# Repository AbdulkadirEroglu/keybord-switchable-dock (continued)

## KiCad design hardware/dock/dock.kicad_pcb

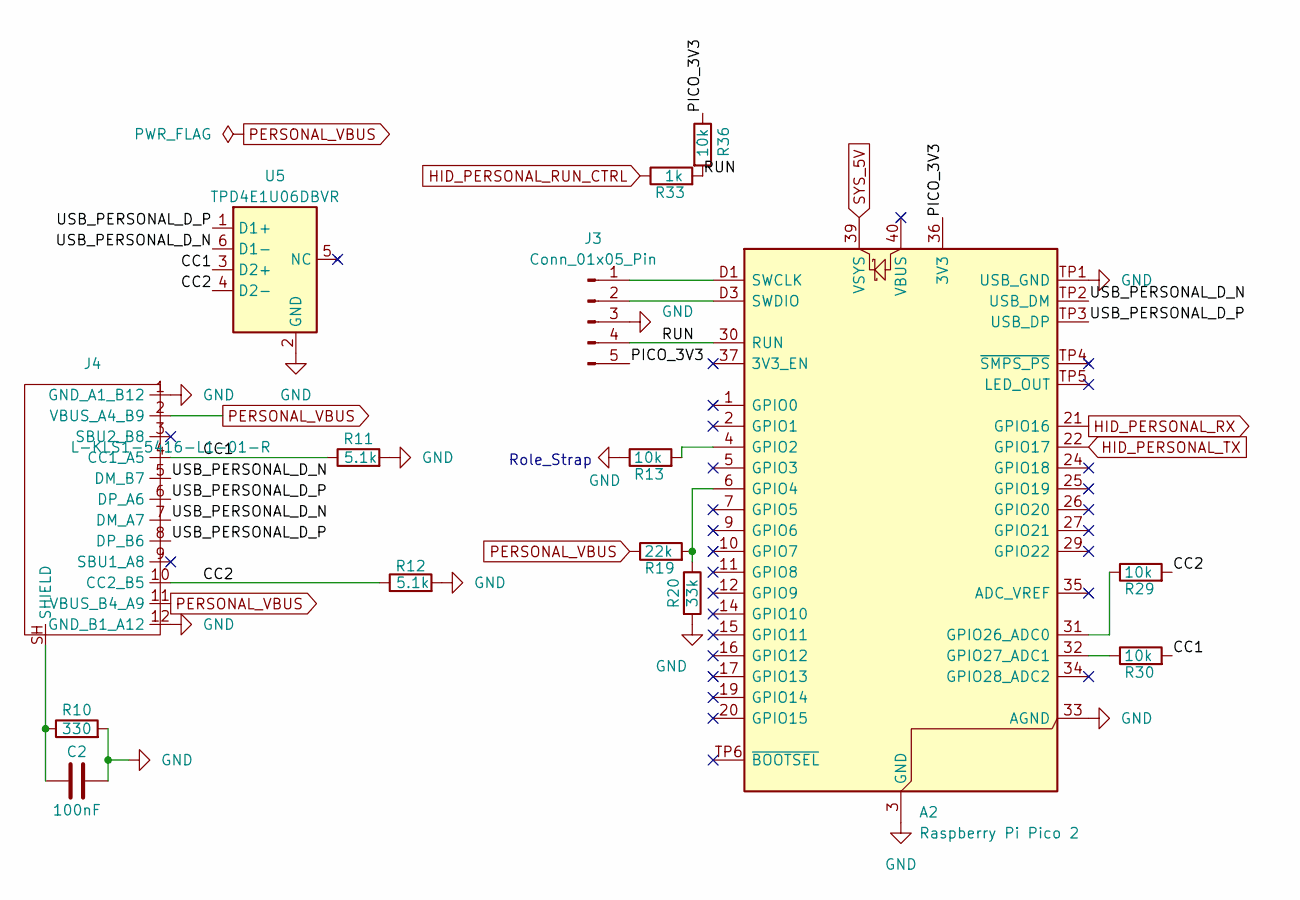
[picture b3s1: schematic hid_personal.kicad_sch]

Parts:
A2: Raspberry Pi Pico 2; RaspberryPi_Pico2_Socket_Pogo
C2: 100nF; C_0805_2012Metric_Pad1.18x1.45mm_HandSolder
J3: Conn_01x05_Pin; PinHeader_1x05_P2.54mm_Vertical
J4: L-KLS1-5416-L1-01-R; KLS L-KLS1-5416-L1-01-R
R10: 330; R_0805_2012Metric_Pad1.20x1.40mm_HandSolder
R11, R12: 5.1k; R_0805_2012Metric_Pad1.20x1.40mm_HandSolder
R13, R29, R30, R36: 10k; R_0805_2012Metric_Pad1.20x1.40mm_HandSolder
R19: 22k; R_0805_2012Metric_Pad1.20x1.40mm_HandSolder
R20: 33k; R_0805_2012Metric_Pad1.20x1.40mm_HandSolder
R33: 1k; R_0805_2012Metric_Pad1.20x1.40mm_HandSolder
U5: TPD4E1U06DBVR; SOT-23-6

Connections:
/HID_PERSONAL/CC1: J4.4 (CC1_A5), R11.1, R30.2, U5.3 (D2+)
/HID_PERSONAL/CC2: J4.10 (CC2_B5), R12.1, R29.2, U5.4 (D2-)
/HID_PERSONAL/PICO_3V3: A2.36 (3V3), J3.5, R36.1
/HID_PERSONAL/RUN: A2.30 (RUN), J3.4, R33.2, R36.2
/HID_PERSONAL/USB_PERSONAL_D_N: A2.TP2 (USB_DM), J4.5 (DM_B7), J4.7 (DM_A7), U5.6 (D1-)
/HID_PERSONAL/USB_PERSONAL_D_P: A2.TP3 (USB_DP), J4.6 (DP_A6), J4.8 (DP_B6), U5.1 (D1+)
GND: A2.3 (GND), A2.8 (GND), A2.13 (GND), A2.18 (GND), A2.23 (GND), A2.28 (GND), A2.33 (AGND), A2.38 (GND), A2.D2 (GND), A2.TP1 (USB_GND), C2.1, J3.3, J4.1 (GND_A1_B12), J4.12 (GND_B1_A12), R10.2, R11.2, R12.2, R13.1, R20.2, U5.2 (GND); also elsewhere on the board
HID_PERSONAL_RUN_CTRL: R33.1; also elsewhere on the board
HID_PERSONAL_RX: A2.21 (GPIO16); also elsewhere on the board
HID_PERSONAL_TX: A2.22 (GPIO17); also elsewhere on the board
unnamed: A2.4 (GPIO2), R13.2
unnamed: A2.6 (GPIO4), R19.2, R20.1
unnamed: A2.31 (GPIO26_ADC0), R29.1
unnamed: A2.32 (GPIO27_ADC1), R30.1
unnamed: A2.D1 (SWCLK), J3.1
unnamed: A2.D3 (SWDIO), J3.2
unnamed: C2.2, J4.SH (SHIELD), R10.1
PERSONAL_VBUS: J4.2 (VBUS_A4_B9), J4.11 (VBUS_B4_A9), R19.1; also elsewhere on the board
SYS_5V: A2.39 (VSYS); also elsewhere on the board

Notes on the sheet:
Role_Strap

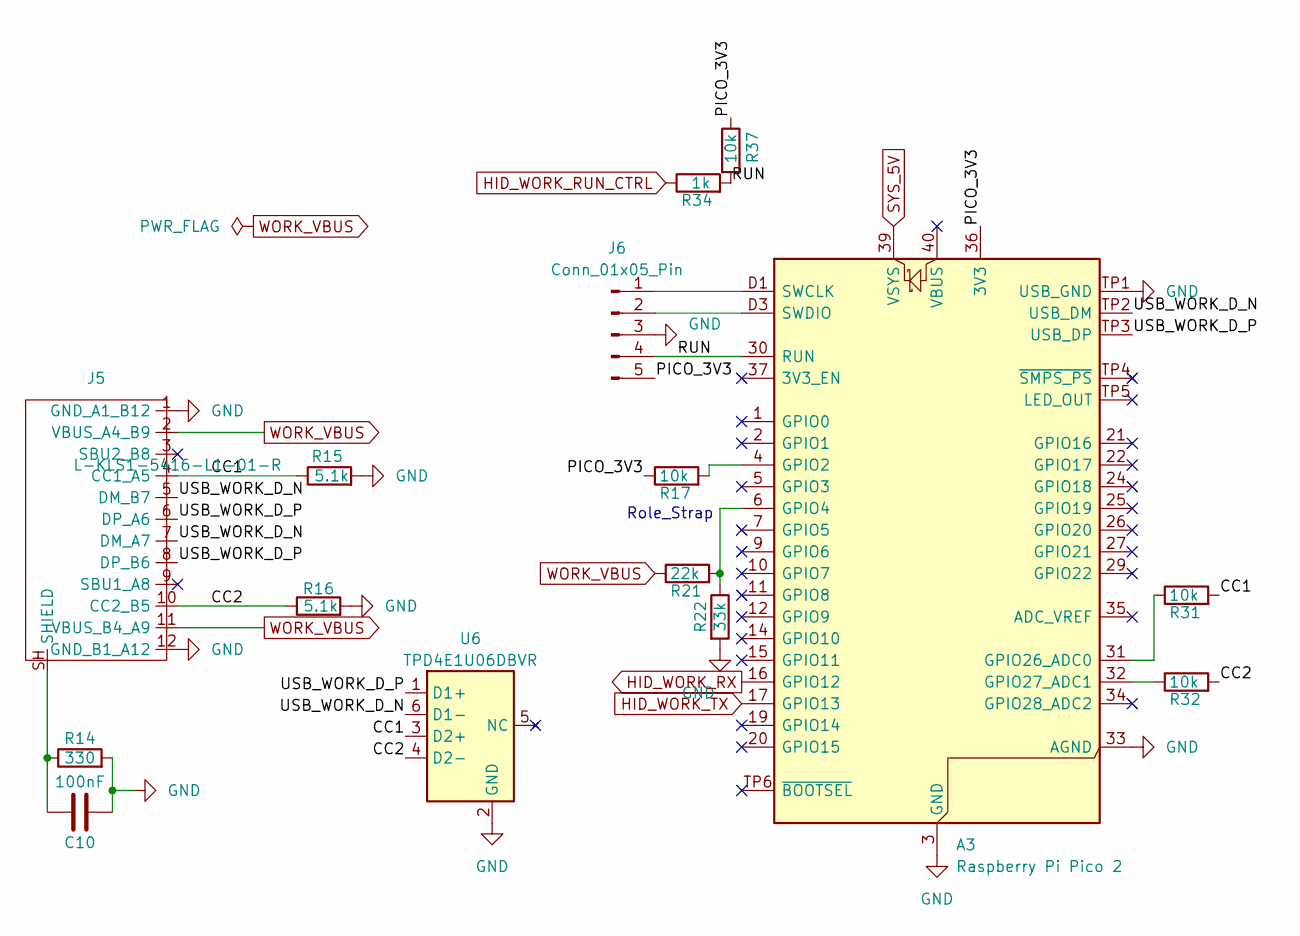
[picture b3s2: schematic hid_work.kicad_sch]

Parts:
A3: Raspberry Pi Pico 2; RaspberryPi_Pico2_Socket_Pogo
C10: 100nF; C_0805_2012Metric_Pad1.18x1.45mm_HandSolder
J5: L-KLS1-5416-L1-01-R; KLS L-KLS1-5416-L1-01-R
J6: Conn_01x05_Pin; PinHeader_1x05_P2.54mm_Vertical
R14: 330; R_0805_2012Metric_Pad1.20x1.40mm_HandSolder
R15, R16: 5.1k; R_0805_2012Metric_Pad1.20x1.40mm_HandSolder
R17, R31, R32, R37: 10k; R_0805_2012Metric_Pad1.20x1.40mm_HandSolder
R21: 22k; R_0805_2012Metric_Pad1.20x1.40mm_HandSolder
R22: 33k; R_0805_2012Metric_Pad1.20x1.40mm_HandSolder
R34: 1k; R_0805_2012Metric_Pad1.20x1.40mm_HandSolder
U6: TPD4E1U06DBVR; SOT-23-6

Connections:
/HID_WORK/CC1: J5.4 (CC1_A5), R15.1, R31.2, U6.3 (D2+)
/HID_WORK/CC2: J5.10 (CC2_B5), R16.1, R32.2, U6.4 (D2-)
/HID_WORK/PICO_3V3: A3.36 (3V3), J6.5, R17.1, R37.1
/HID_WORK/RUN: A3.30 (RUN), J6.4, R34.2, R37.2
/HID_WORK/USB_WORK_D_N: A3.TP2 (USB_DM), J5.5 (DM_B7), J5.7 (DM_A7), U6.6 (D1-)
/HID_WORK/USB_WORK_D_P: A3.TP3 (USB_DP), J5.6 (DP_A6), J5.8 (DP_B6), U6.1 (D1+)
GND: A3.3 (GND), A3.8 (GND), A3.13 (GND), A3.18 (GND), A3.23 (GND), A3.28 (GND), A3.33 (AGND), A3.38 (GND), A3.D2 (GND), A3.TP1 (USB_GND), C10.2, J5.1 (GND_A1_B12), J5.12 (GND_B1_A12), J6.3, R14.2, R15.2, R16.2, R22.2, U6.2 (GND); also elsewhere on the board
HID_WORK_RUN_CTRL: R34.1; also elsewhere on the board
HID_WORK_RX: A3.16 (GPIO12); also elsewhere on the board
HID_WORK_TX: A3.17 (GPIO13); also elsewhere on the board
unnamed: A3.4 (GPIO2), R17.2
unnamed: A3.6 (GPIO4), R21.2, R22.1
unnamed: A3.31 (GPIO26_ADC0), R31.1
unnamed: A3.32 (GPIO27_ADC1), R32.1
unnamed: A3.D1 (SWCLK), J6.1
unnamed: A3.D3 (SWDIO), J6.2
unnamed: C10.1, J5.SH (SHIELD), R14.1
SYS_5V: A3.39 (VSYS); also elsewhere on the board
WORK_VBUS: J5.2 (VBUS_A4_B9), J5.11 (VBUS_B4_A9), R21.1; also elsewhere on the board

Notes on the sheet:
Role_Strap

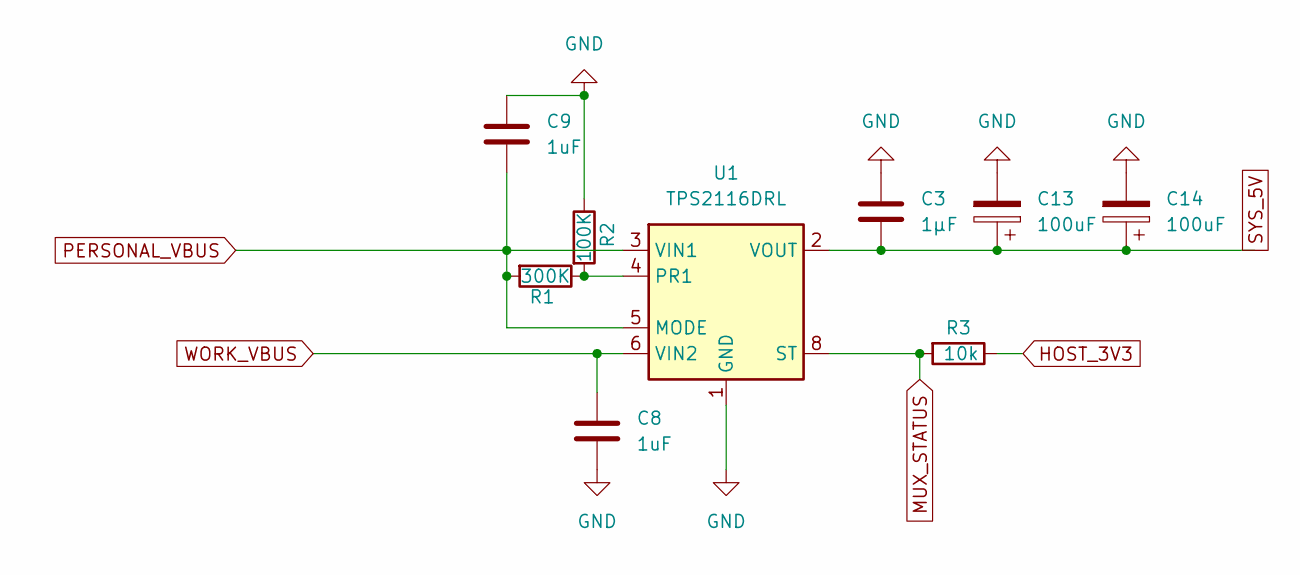
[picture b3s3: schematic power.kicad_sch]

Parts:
C3: 1µF; C_0805_2012Metric_Pad1.18x1.45mm_HandSolder
C8, C9: 1uF; C_0805_2012Metric_Pad1.18x1.45mm_HandSolder
C13, C14: 100uF; CP_Elec_6.3x7.7
R1: 300K; R_0805_2012Metric_Pad1.20x1.40mm_HandSolder
R2: 100K; R_0805_2012Metric_Pad1.20x1.40mm_HandSolder
R3: 10k; R_0805_2012Metric_Pad1.20x1.40mm_HandSolder
U1: TPS2116DRL; SOT-583-8_HandSolder

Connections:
GND: C3.1, C8.2, C9.1, C13.2, C14.2, R2.1, U1.1 (GND); also elsewhere on the board
HOST_3V3: R3.1; also elsewhere on the board
MUX_STATUS: R3.2, U1.8 (ST); also elsewhere on the board
unnamed: R1.1, R2.2, U1.4 (PR1)
PERSONAL_VBUS: C9.2, R1.2, U1.3 (VIN1), U1.5 (MODE); also elsewhere on the board
SYS_5V: C3.2, C13.1, C14.1, U1.2 (VOUT), U1.7 (VOUT); also elsewhere on the board
WORK_VBUS: C8.1, U1.6 (VIN2); also elsewhere on the board

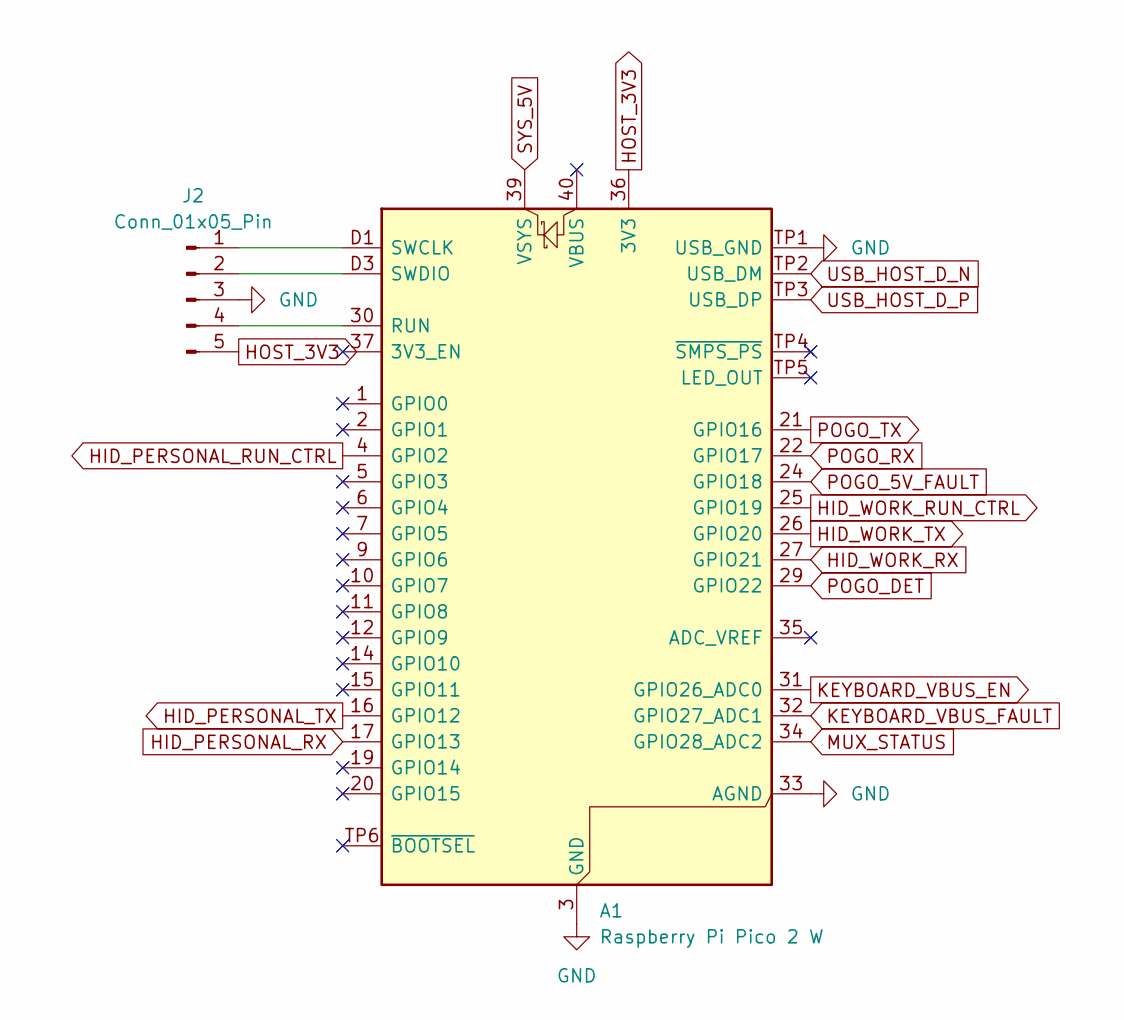
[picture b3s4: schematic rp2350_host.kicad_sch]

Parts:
A1: Raspberry Pi Pico 2 W; RaspberryPi_Pico2W_Socket_Pogo
J2: Conn_01x05_Pin; PinHeader_1x05_P2.54mm_Vertical

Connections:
GND: A1.3 (GND), A1.8 (GND), A1.13 (GND), A1.18 (GND), A1.23 (GND), A1.28 (GND), A1.33 (AGND), A1.38 (GND), A1.D2 (GND), A1.TP1 (USB_GND), J2.3; also elsewhere on the board
HID_PERSONAL_RUN_CTRL: A1.4 (GPIO2); also elsewhere on the board
HID_PERSONAL_RX: A1.17 (GPIO13); also elsewhere on the board
HID_PERSONAL_TX: A1.16 (GPIO12); also elsewhere on the board
HID_WORK_RUN_CTRL: A1.25 (GPIO19); also elsewhere on the board
HID_WORK_RX: A1.27 (GPIO21); also elsewhere on the board
HID_WORK_TX: A1.26 (GPIO20); also elsewhere on the board
HOST_3V3: A1.36 (3V3), J2.5; also elsewhere on the board
KEYBOARD_VBUS_EN: A1.31 (GPIO26_ADC0); also elsewhere on the board
KEYBOARD_VBUS_FAULT: A1.32 (GPIO27_ADC1); also elsewhere on the board
MUX_STATUS: A1.34 (GPIO28_ADC2); also elsewhere on the board
unnamed: A1.30 (RUN), J2.4
unnamed: A1.D1 (SWCLK), J2.1
unnamed: A1.D3 (SWDIO), J2.2
POGO_5V_FAULT: A1.24 (GPIO18); also elsewhere on the board
POGO_DET: A1.29 (GPIO22); also elsewhere on the board
POGO_RX: A1.22 (GPIO17); also elsewhere on the board
POGO_TX: A1.21 (GPIO16); also elsewhere on the board
SYS_5V: A1.39 (VSYS); also elsewhere on the board
USB_HOST_D_N: A1.TP2 (USB_DM); also elsewhere on the board
USB_HOST_D_P: A1.TP3 (USB_DP); also elsewhere on the board

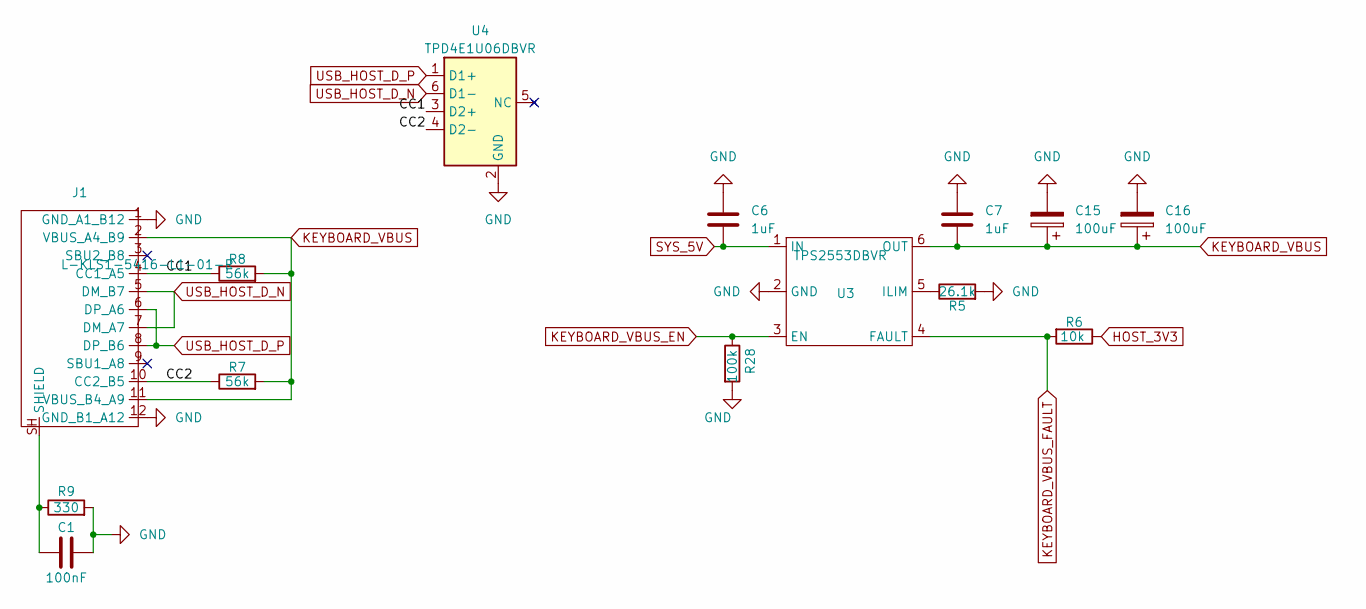
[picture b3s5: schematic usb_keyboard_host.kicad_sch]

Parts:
C1: 100nF; C_0805_2012Metric_Pad1.18x1.45mm_HandSolder
C6, C7: 1uF; C_0805_2012Metric_Pad1.18x1.45mm_HandSolder
C15, C16: 100uF; CP_Elec_6.3x7.7
J1: L-KLS1-5416-L1-01-R; KLS L-KLS1-5416-L1-01-R
R5: 26.1k; R_0805_2012Metric_Pad1.20x1.40mm_HandSolder
R6: 10k; R_0805_2012Metric_Pad1.20x1.40mm_HandSolder
R7, R8: 56k; R_0805_2012Metric_Pad1.20x1.40mm_HandSolder
R9: 330; R_0805_2012Metric_Pad1.20x1.40mm_HandSolder
R28: 100k; R_0805_2012Metric_Pad1.20x1.40mm_HandSolder
U3: TPS2553DBVR; SOT-23-6
U4: TPD4E1U06DBVR; SOT-23-6

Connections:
/USB_KEYBOARD_HOST/CC1: J1.4 (CC1_A5), R8.1, U4.3 (D2+)
/USB_KEYBOARD_HOST/CC2: J1.10 (CC2_B5), R7.1, U4.4 (D2-)
GND: C1.1, C6.1, C7.1, C15.2, C16.2, J1.1 (GND_A1_B12), J1.12 (GND_B1_A12), R5.2, R9.2, R28.2, U3.2 (GND), U4.2 (GND); also elsewhere on the board
HOST_3V3: R6.1; also elsewhere on the board
KEYBOARD_VBUS: C7.2, C15.1, C16.1, J1.2 (VBUS_A4_B9), J1.11 (VBUS_B4_A9), R7.2, R8.2, U3.6 (OUT)
KEYBOARD_VBUS_EN: R28.1, U3.3 (EN); also elsewhere on the board
KEYBOARD_VBUS_FAULT: R6.2, U3.4 (FAULT); also elsewhere on the board
unnamed: C1.2, J1.SH (SHIELD), R9.1
unnamed: R5.1, U3.5 (ILIM)
SYS_5V: C6.2, U3.1 (IN); also elsewhere on the board
USB_HOST_D_N: J1.5 (DM_B7), J1.7 (DM_A7), U4.6 (D1-); also elsewhere on the board
USB_HOST_D_P: J1.6 (DP_A6), J1.8 (DP_B6), U4.1 (D1+); also elsewhere on the board

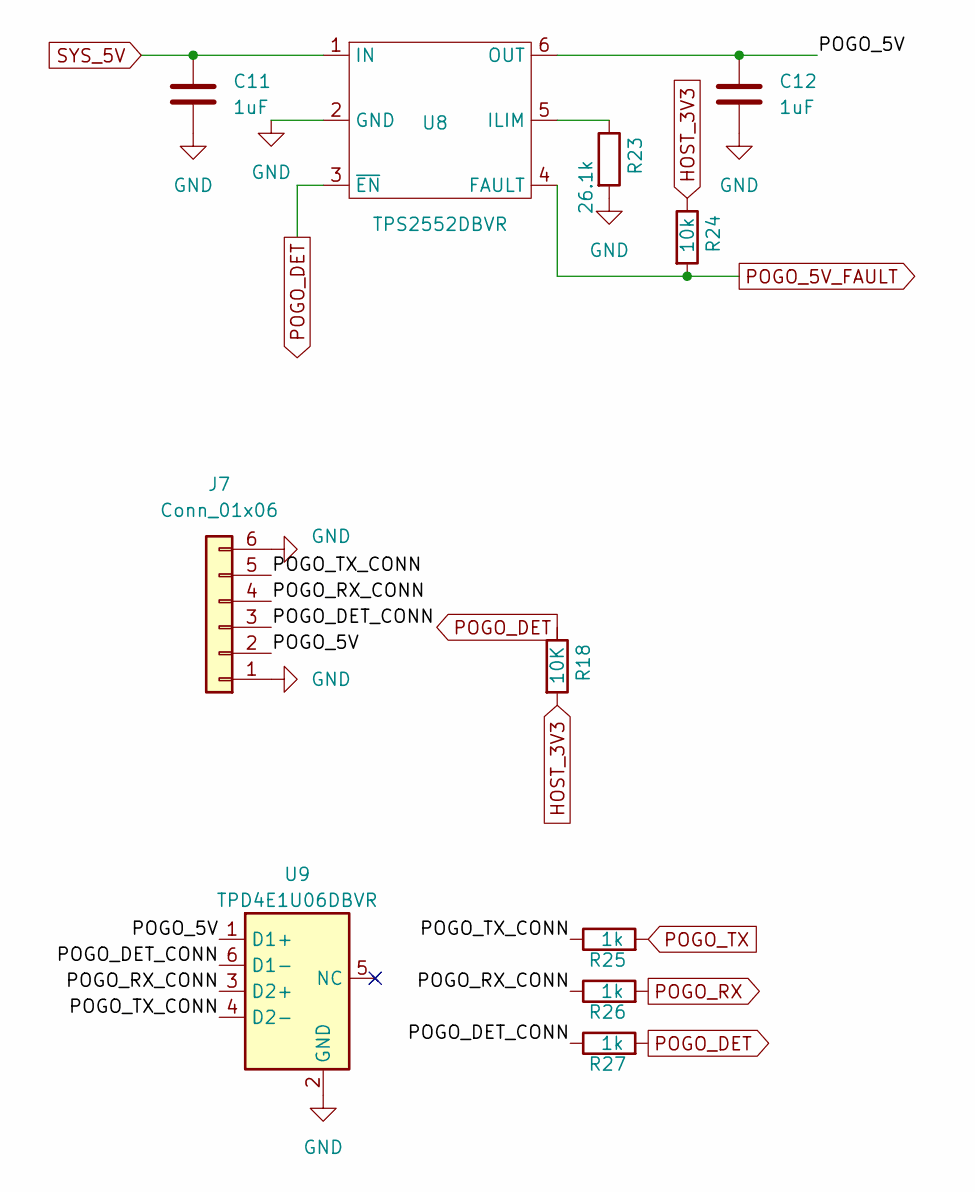
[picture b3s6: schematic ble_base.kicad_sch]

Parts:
C11, C12: 1uF; C_0805_2012Metric_Pad1.18x1.45mm_HandSolder
J7: Conn_01x06; Pogo-6
R18: 10K; R_0805_2012Metric_Pad1.20x1.40mm_HandSolder
R23: 26.1k; R_0805_2012Metric_Pad1.20x1.40mm_HandSolder
R24: 10k; R_0805_2012Metric_Pad1.20x1.40mm_HandSolder
R25, R26, R27: 1k; R_0805_2012Metric_Pad1.20x1.40mm_HandSolder
U8: TPS2552DBVR; SOT-23-6
U9: TPD4E1U06DBVR; SOT-23-6

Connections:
/BLE_BASE/POGO_5V: C12.1, J7.2, U8.6 (OUT), U9.1 (D1+)
/BLE_BASE/POGO_DET_CONN: J7.3, R27.1, U9.6 (D1-)
/BLE_BASE/POGO_RX_CONN: J7.4, R26.1, U9.3 (D2+)
/BLE_BASE/POGO_TX_CONN: J7.5, R25.1, U9.4 (D2-)
GND: C11.2, C12.2, J7.1, J7.6, R23.2, U8.2 (GND), U9.2 (GND); also elsewhere on the board
HOST_3V3: R18.2, R24.1; also elsewhere on the board
unnamed: R23.1, U8.5 (ILIM)
POGO_5V_FAULT: R24.2, U8.4 (FAULT); also elsewhere on the board
POGO_DET: R18.1, R27.2, U8.3 (~EN); also elsewhere on the board
POGO_RX: R26.2; also elsewhere on the board
POGO_TX: R25.2; also elsewhere on the board
SYS_5V: C11.1, U8.1 (IN); also elsewhere on the board

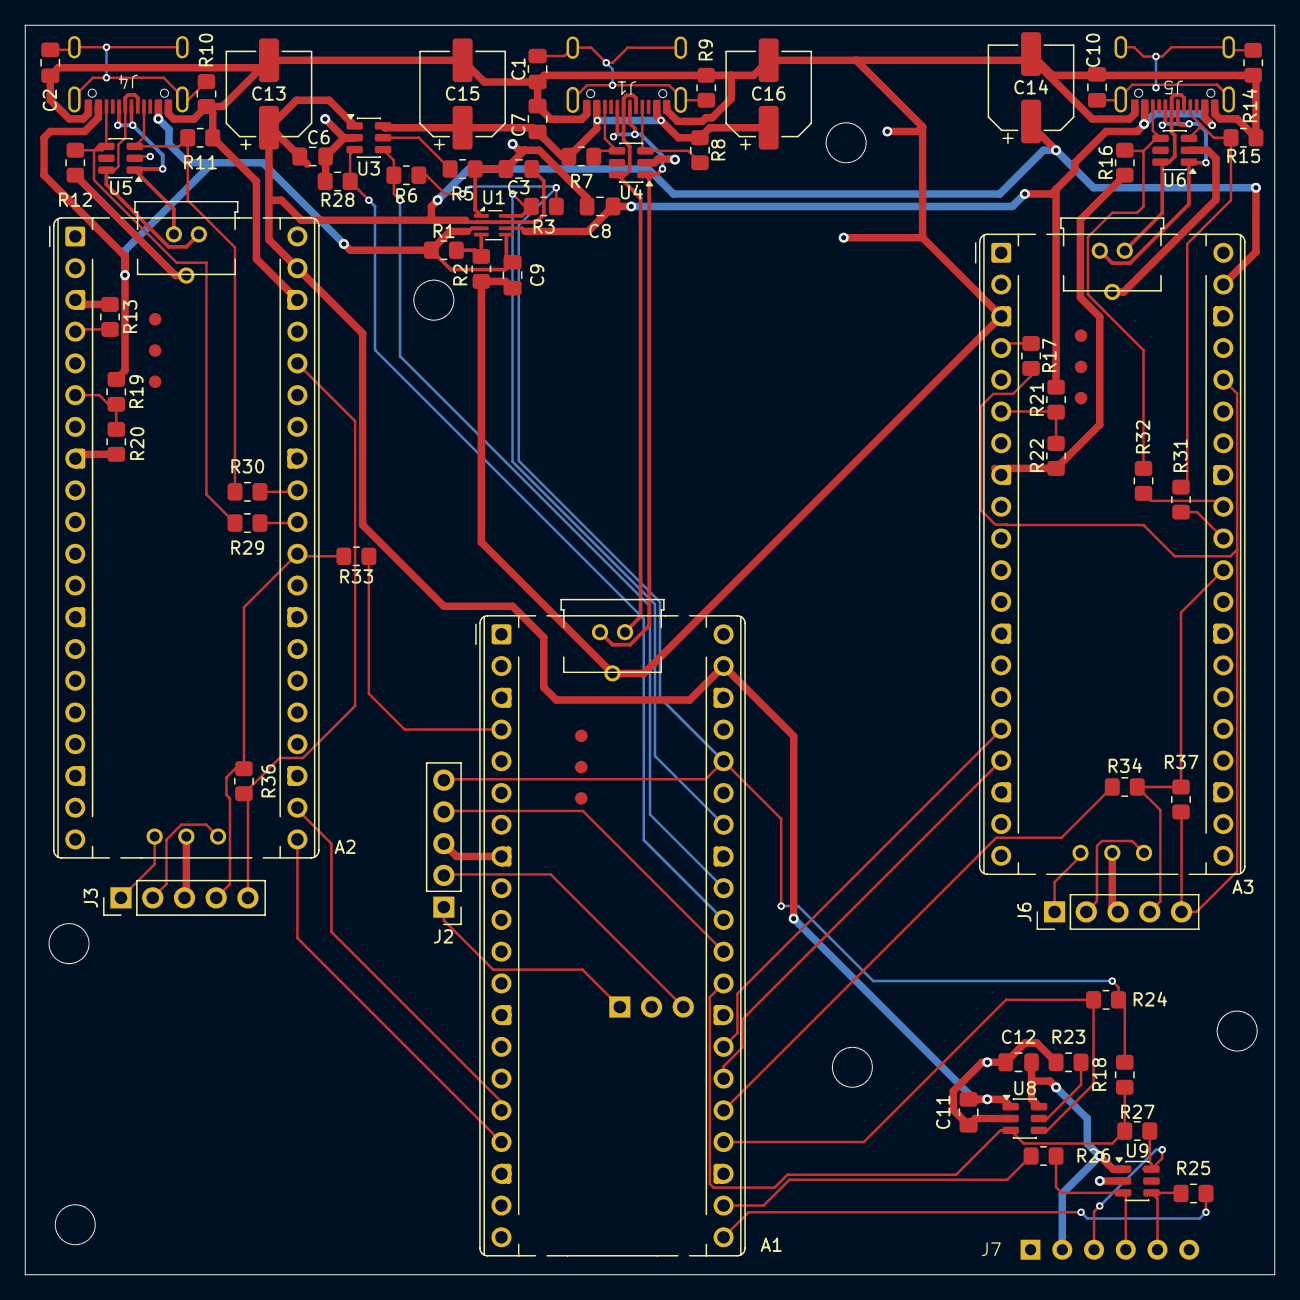
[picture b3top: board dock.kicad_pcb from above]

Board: 2 copper layers, 100.0 x 100.0 mm, 72 parts (0 on the bottom side), 60 nets.

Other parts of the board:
H1, H2, H3, H4, H5, H6: MountingHole_3.2mm_M3

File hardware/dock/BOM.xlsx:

Dock-pad — Dock PCB bill of materials
Generated from the hardware/dock schematic (66 parts) plus mechanical items. Pr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
Boards to build |  | 1 |  | How to use:
Total cost (TL) |  | 3499.961 |  | Yellow cells are yours to edit: boards to build, spares, pack size, price per p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
Lines with a price |  | 25 |  | Black cells are formulas: Needed = Qty/board × Boards + Spares; Packs = ROUNDUP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
Lines still missing a price |  | 0 |  | Blue prices were seen on the listed shop on 2026-09-24 — verify before ordering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
USD → TL rate |  | 48.92
# | Group | Refs | Description | Part number | Package / footprint | Qty / board | Spares | Needed | Pack size | Packs to order | Price per pack (TL) | Line total (TL) | Shop | URL | Notes
1 | Modules | A1 | Host + BLE module | Raspberry Pi Pico 2 W | Socketed, 2×20 headers | 1 | 0 | 1 | 1 | 1 | 559.61 | 559.61 | Robotistan | https://www.robotistan.com/raspberry-pi-pico-2-w-header | Solder male 1×20 headers + a 1×3 header on the debug holes (pointing down)
2 | Modules | A2, A3 | HID endpoint modules | Raspberry Pi Pico 2 | Socketed, 2×20 headers | 2 | 0 | 2 | 1 | 2 | 416.24 | 832.48 | Robotistan | https://www.robotistan.com/raspberry-pi-pico-2-header?langua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 | Solder male 1×20 headers (pointing down)
3 | ICs | U1 | Priority power mux 2.5 A | TPS2116DRLR | SOT-583-8 (hand-solder footprint) | 1 | 4 | 5 | 1 | 5 | 34.31 | 171.55 | tme | https://www.tme.eu/tr/tr/details/tps2116drlr/analog-coklayic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 | Seen at LCSC for ~0.25 USD (2026-09-24). Tiny 0.5 mm pitch — spares recommended
4 | ICs | U3 | USB power switch, active-high EN | TPS2553DBVR | SOT-23-6 | 1 | 1 | 2 | 1 | 2 | 26.81 | 53.62 | Özdisan | https://ozdisan.com/integrated-circuits-ics/power-management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 | Price seen 2026-09-24 (1 pc) — verify before ordering
5 | ICs | U8 | USB power switch, active-low EN | TPS2552DBVR | SOT-23-6 | 1 | 1 | 2 | 1 | 2 | 27.02 | 54.04 | Özdisan | https://ozdisan.com/integrated-circuits-ics/power-management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 | Price seen 2026-09-24 (1 pc) — verify before ordering. Not the -1 (latch-off) v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
6 | ICs | U4, U5, U6, U9 | 4-channel ESD protection | TPD4E1U06DBVR | SOT-23-6 | 4 | 2 | 6 | 1 | 6 | 11.88 | 71.28 | Özdisan | https://ozdisan.com/power-semiconductors/diodes-diode-module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 | Price seen 2026-09-24 (1 pc) — verify before ordering
7 | Connectors | J1, J4, J5 | USB-C receptacle, USB 2.0, 16-pin SMD | KLS L-KLS1-5416-L1-01-R | USB-C 16-pin SMD | 3 | 2 | 5 | 1 | 5 | 4.164 | 20.82 | Özdisan | https://www.ozdisan.com/p/usb-konnektorler-357/kls-electroni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 | Fine-pitch pads — spares for practice
8 | Connectors | J7 | Pogo connector, 6-pin, 2.54 mm | (choose — must mate with the pad side) | THT 1×6, 2.54 mm | 1 | 0 | 1 | 1 | 1 | 360 | 360 | Motorbit | https://www.motorobit.com/6-pin-254mm-90c-pogo-pin-magnetic-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 | GND | +5V | DET | RX | TX | GND
9 | Connectors | J2, J3, J6 | SWD header 1×5, 2.54 mm | Male pin header 1×5 | THT | 3 | 0 | 3 | 8 | 1 | 3.6 | 3.6 | Motorbit | https://www.motorobit.com/1x40-erkek-header-40-pin-254mm-180-derece | Can be cut from a 1×40 strip
10 | Capacitors | C13, C14, C15, C16 | Bulk capacitor 100 µF 25 V, 105 °C | Panasonic EEE-FK1E101XP | 6.3 × 7.7 mm SMD can | 4 | 1 | 5 | 1 | 5 | 14.33 | 71.65 | Özdisan | https://www.ozdisan.com/passive-components/capacitors/alumin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 | Price seen 2026-09-24 (1 pc) — verify before ordering. Polarized: stripe = −
11 | Capacitors | C3, C6, C7, C8, C9, C11, C12 | 1 µF, ≥10 V, X7R | samsung CL21B105KBFNNNE | 0805 capacitor | 7 | 13 | 20 | 1 | 20 | 1.26923 | 25.3846 | Özdisan | https://www.ozdisan.com/p/smt-smd-ve-mlcc-kapasitorler-184/s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
12 | Capacitors | C1, C2, C10 | 100 nF, ≥16 V, X7R | samsung CL21B104KBCNNNC | 0805 capacitor | 3 | 17 | 20 | 1 | 20 | 0.5274 | 10.548 | Özdisan | https://www.ozdisan.com/p/smt-smd-ve-mlcc-kapasitorler-184/s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 | Shield termination
13 | Resistors | R3, R6, R13, R17, R18, R24, R29, R30, R31, R32, R36, R37 | 10 kΩ 1% | 0805S8F1002T5E | 0805 resistor | 12 | 3 | 15 | 100 | 1 | 10.68 | 10.68 | Özdisan | https://www.ozdisan.com/p/smt-smd-ve-cip-direncler-194/royal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
14 | Resistors | R25, R26, R27, R33, R34 | 1 kΩ 1% | RC0805FR-071KL | 0805 resistor | 5 | 2 | 7 | 50 | 1 | 12.6 | 12.6 | Özdisan | https://www.ozdisan.com/p/smt-smd-ve-cip-direncler-194/yageo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
15 | Resistors | R11, R12, R15, R16 | 5.1 kΩ 1% | 0805S8F5101T5E | 0805 resistor | 4 | 2 | 6 | 100 | 1 | 10.68 | 10.68 | Özdisan | https://www.ozdisan.com/p/smt-smd-ve-cip-direncler-194/royal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 | USB-C CC pull-downs
16 | Resistors | R9, R10, R14 | 330 Ω 1% | 0805S8F3300T5E | 0805 resistor | 3 | 2 | 5 | 100 | 1 | 10.68 | 10.68 | Özdisan | https://www.ozdisan.com/p/smt-smd-ve-cip-direncler-194/royal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
17 | Resistors | R5, R23 | 26.1 kΩ 1% | 0805S8F2612T5E | 0805 resistor | 2 | 2 | 4 | 100 | 1 | 7.26 | 7.26 | Özdisan | https://www.ozdisan.com/p/smt-smd-ve-cip-direncler-194/royal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 | Sets the 1 A current limit (U3, U8)
18 | Resistors | R7, R8 | 56 kΩ 1% | 0805S8F5602T5E | 0805 resistor | 2 | 2 | 4 | 100 | 1 | 10.68 | 10.68 | Özdisan | https://www.ozdisan.com/p/smt-smd-ve-cip-direncler-194/royal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 | Keyboard-port CC pull-ups
19 | Resistors | R19, R21 | 22 kΩ 1% | 0805S8F2202T5E | 0805 resistor | 2 | 2 | 4 | 100 | 1 | 10.68 | 10.68 | Özdisan | https://www.ozdisan.com/p/smt-smd-ve-cip-direncler-194/royal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 | VBUS sense divider (top)
20 | Resistors | R20, R22 | 33 kΩ 1% | 0805S8F3302T5E | 0805 resistor | 2 | 2 | 4 | 100 | 1 | 10.68 | 10.68 | Özdisan | https://www.ozdisan.com/p/smt-smd-ve-cip-direncler-194/royal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 | VBUS sense divider (bottom)
21 | Resistors | R2, R28 | 100 kΩ 1% | 0805S8F1003T5E | 0805 resistor | 2 | 2 | 4 | 100 | 1 | 10.68 | 10.68 | Özdisan | https://www.ozdisan.com/p/smt-smd-ve-cip-direncler-194/royal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
22 | Resistors | R1 | 300 kΩ 1% | 0805S8F3003T5E | 0805 resistor | 1 | 2 | 3 | 100 | 1 | 10.68 | 10.68 | Özdisan |  | TPS2116 PR1 divider (≈4.0 V switchover)
23 | Mechanical | — | Female socket 2.54 mm, 8.5 mm tall (cut from 1×40) | generic | THT | 6 | 3 | 9 | 2 | 5 | 6.6 | 33 | motorbit | https://www.motorobit.com/1x40-disi-header-40-pin-180-derece | One 1×40 strip gives one 1×20 + one 1×19 (a pin is lost at the cut). Put the 1×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
27 | Mechanical | — | Spring probe P50-B1 | P50-B1 | 0.68 mm barrel, 16.35 mm | 15 | 0 | 15 | 100 | 1 | 270 | 270 | motorbit | https://www.motorobit.com/yayli-pogo-p50-b1-test-probu-100-adet | 10 required + 5 optional (GND). Sold as 100-pack; price seen 2026-09-24 — verify
28 | PCB | — | Dock PCB, 2-layer, 100 × 100 mm, 1.6 mm, HASL | JLCPCB / PCBWay | — | 1 | 0 | 1 | 5 | 1 | 857.0784 | 857.0784 | JLCPCB |  | 17.52 USD for 5 boards incl. e-post shipping to my address (JLCPCB quote 2026-0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
 |  |  |  |  |  |  |  |  |  |  | Total | 3499.961
